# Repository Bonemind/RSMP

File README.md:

# RSMP

AKA "Rockstars Macropad". A [KMK](https://github.com/KMKfw/kmk_firmware) and Raspberry pi based 20 key macropad. The macropad is direct pin, meaning every button uses a dedication gpio pin, so no diodes are needed.

This was created for a workshop at [Team Rockstars IT](https://www.teamrockstars.nl/)

## BOM

  - Raspberry Pi Pico. Make sure you get the variant with gpio pins 16/17 in the bottom right
  - 20 Cherry MX compatible switches
  - 20 Cherry MX keycaps
  - Main PCB
  - Bottom plate PCB
  - 8x M2.5 screws
  - 4 Spacers
  - Those round bumper things you stick under something to make it non-slip

## Software

  - Dowload the [Circuitpython](https://circuitpython.org/) release for the pico board.
  - Plug in the pi pico while holding the "boot" button
  - Copy the circuitpython Uf2 to the root of the device
  - It should now reboot, and you should have a "CIRCUITPY" storage device
  - Remove the `code.py` file from the storage device
  - Copy all files from the `firmware` folder to the root of the drive
  - Replug the device

It should now behave as a keyboard.

### Firmware

This macropad uses KMK for it's firmware. KMK is a flexible circuitpython based project for mechanical keyboards that offers a lot of options. The basic firmware for the RSMP is simple, in that every button outputs a letter. To customize the behavior, you can modify `main.py`.

As an example of layers, the bottom left button will output a space when tapped, and when held, the buttons will output numbers and various symbols instead of letters.

## Credits

  - [KMK](https://github.com/KMKfw/kmk_firmware) - Keyboard software
  - [ncarandini](https://github.com/ncarandini/KiCad-RP-Pico) - Kicad pi pico footprint and model
  - [foostan](https://github.com/foostan/kbd) - Keyboard switch footprints

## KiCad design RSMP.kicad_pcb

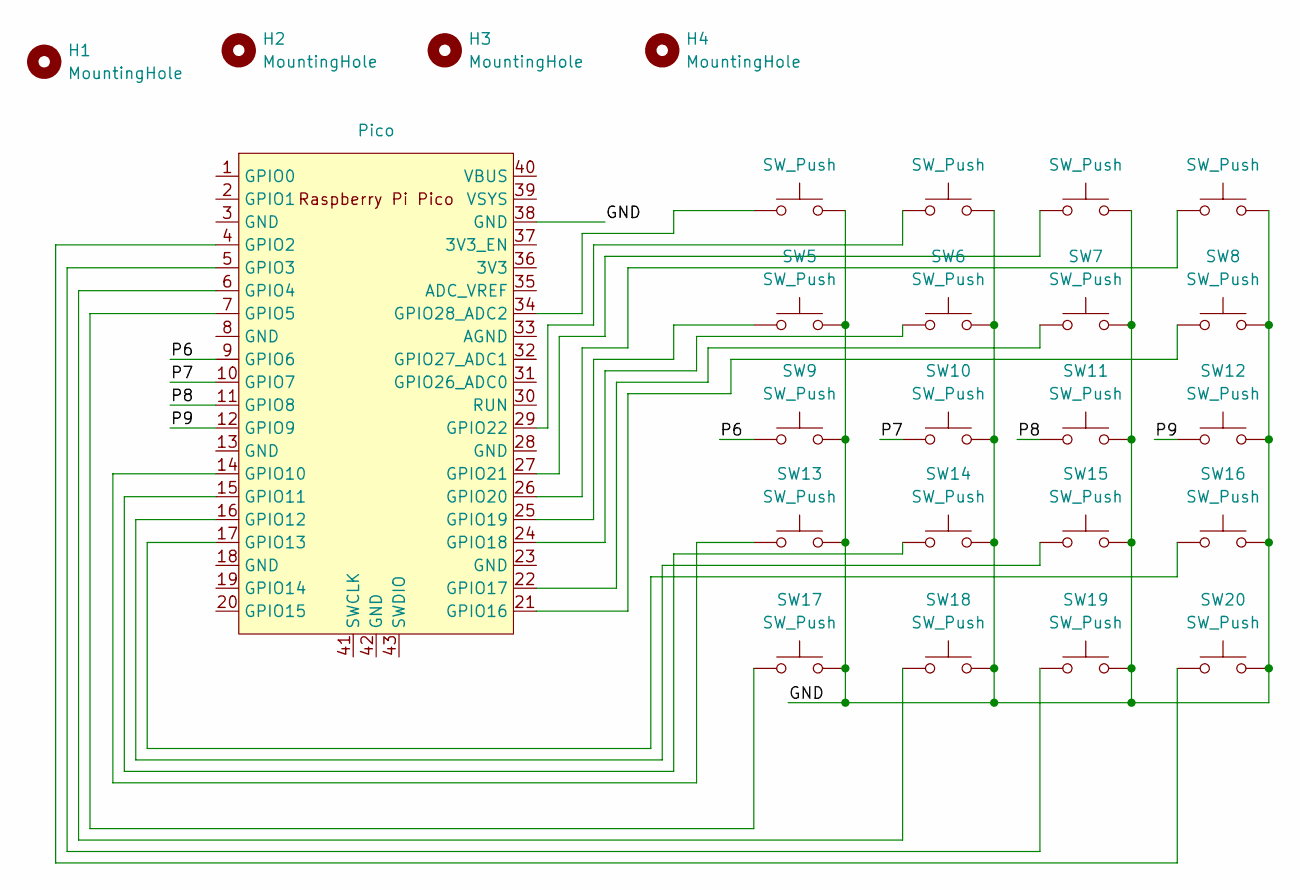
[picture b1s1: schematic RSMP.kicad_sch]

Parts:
H1, H2, H3, H4: MountingHole; MountingHole_2.7mm_M2.5
SW1, SW2, SW3, SW4, SW5, SW6, SW7, SW8, SW9, SW10, SW11, SW12, SW13, SW14, SW15, SW16, SW17, SW18, SW19, SW20: SW_Push; SW_Cherry_MX_1.00u_PCB
U1: Pico; RPi_Pico_SMD_TH

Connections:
/GND: SW1.2, SW2.2, SW3.2, SW4.2, SW5.2, SW6.2, SW7.2, SW8.2, SW9.2, SW10.2, SW11.2, SW12.2, SW13.2, SW14.2, SW15.2, SW16.2, SW17.2, SW18.2, SW19.2, SW20.2, U1.38 (GND)
/P6: SW9.1, U1.9 (GPIO6)
/P7: SW10.1, U1.10 (GPIO7)
/P8: SW11.1, U1.11 (GPIO8)
/P9: SW12.1, U1.12 (GPIO9)
unnamed: SW20.1, U1.4 (GPIO2)
unnamed: SW19.1, U1.5 (GPIO3)
unnamed: SW18.1, U1.6 (GPIO4)
unnamed: SW17.1, U1.7 (GPIO5)
unnamed: SW13.1, U1.14 (GPIO10)
unnamed: SW14.1, U1.15 (GPIO11)
unnamed: SW15.1, U1.16 (GPIO12)
unnamed: SW16.1, U1.17 (GPIO13)
unnamed: SW8.1, U1.21 (GPIO16)
unnamed: SW7.1, U1.22 (GPIO17)
unnamed: SW6.1, U1.24 (GPIO18)
unnamed: SW5.1, U1.25 (GPIO19)
unnamed: SW4.1, U1.26 (GPIO20)
unnamed: SW3.1, U1.27 (GPIO21)
unnamed: SW2.1, U1.29 (GPIO22)
unnamed: SW1.1, U1.34 (GPIO28_ADC2)

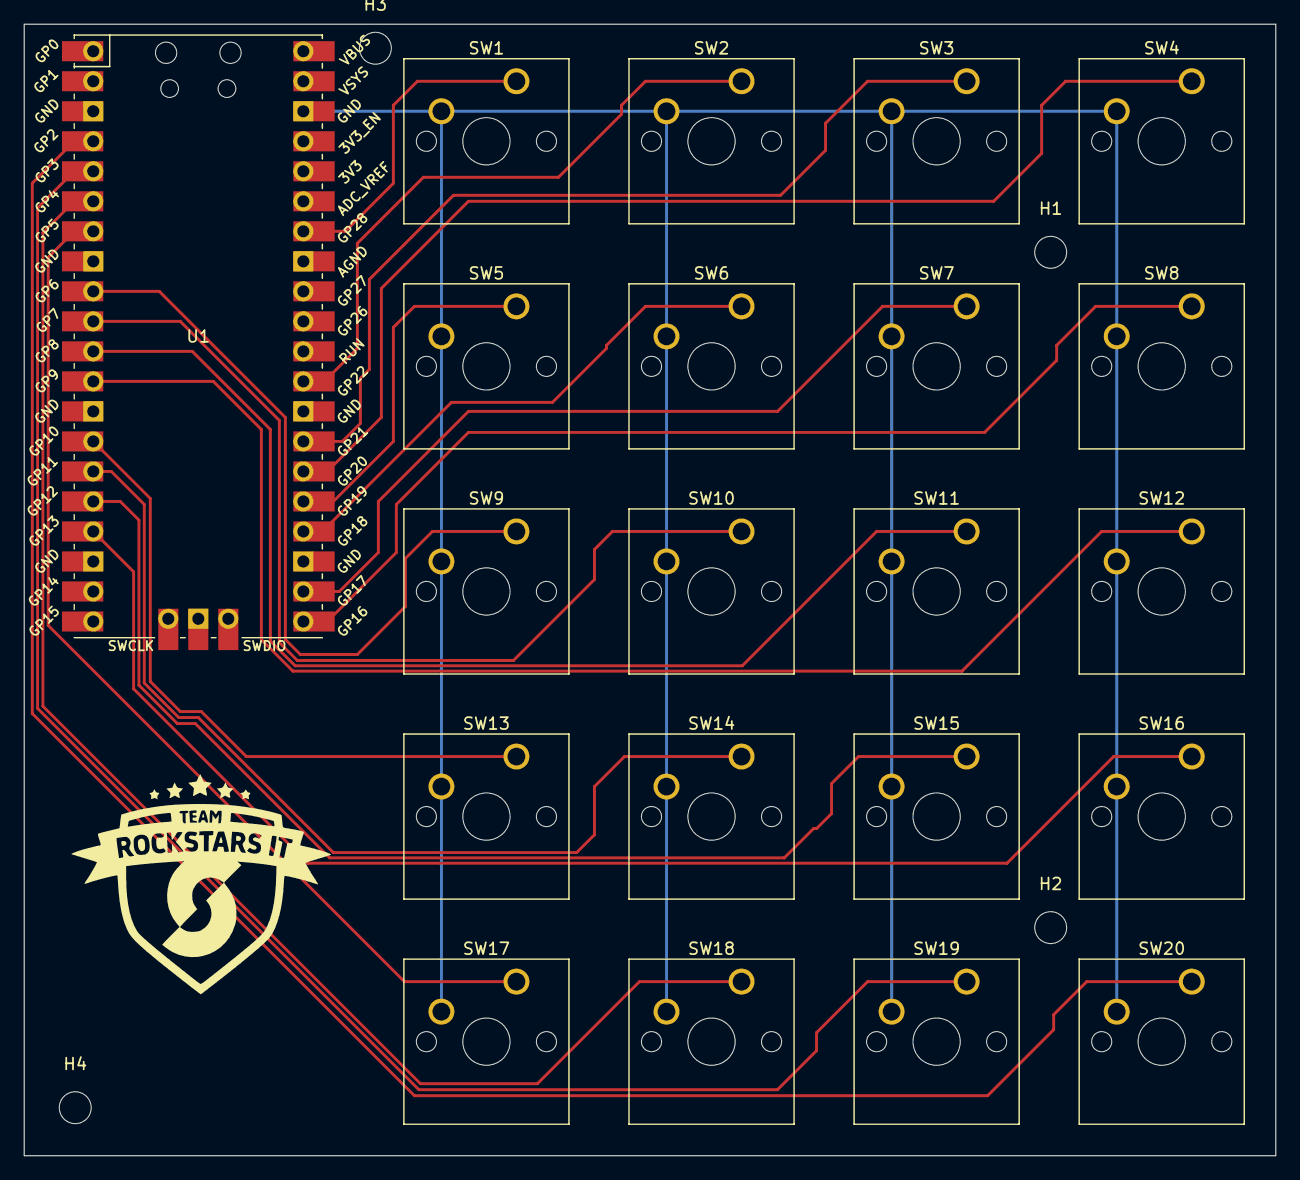
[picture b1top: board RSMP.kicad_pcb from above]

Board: 2 copper layers, 105.9 x 95.8 mm, 25 parts (0 on the bottom side), 21 nets.

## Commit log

2024-04-19 update kmk, add layers
